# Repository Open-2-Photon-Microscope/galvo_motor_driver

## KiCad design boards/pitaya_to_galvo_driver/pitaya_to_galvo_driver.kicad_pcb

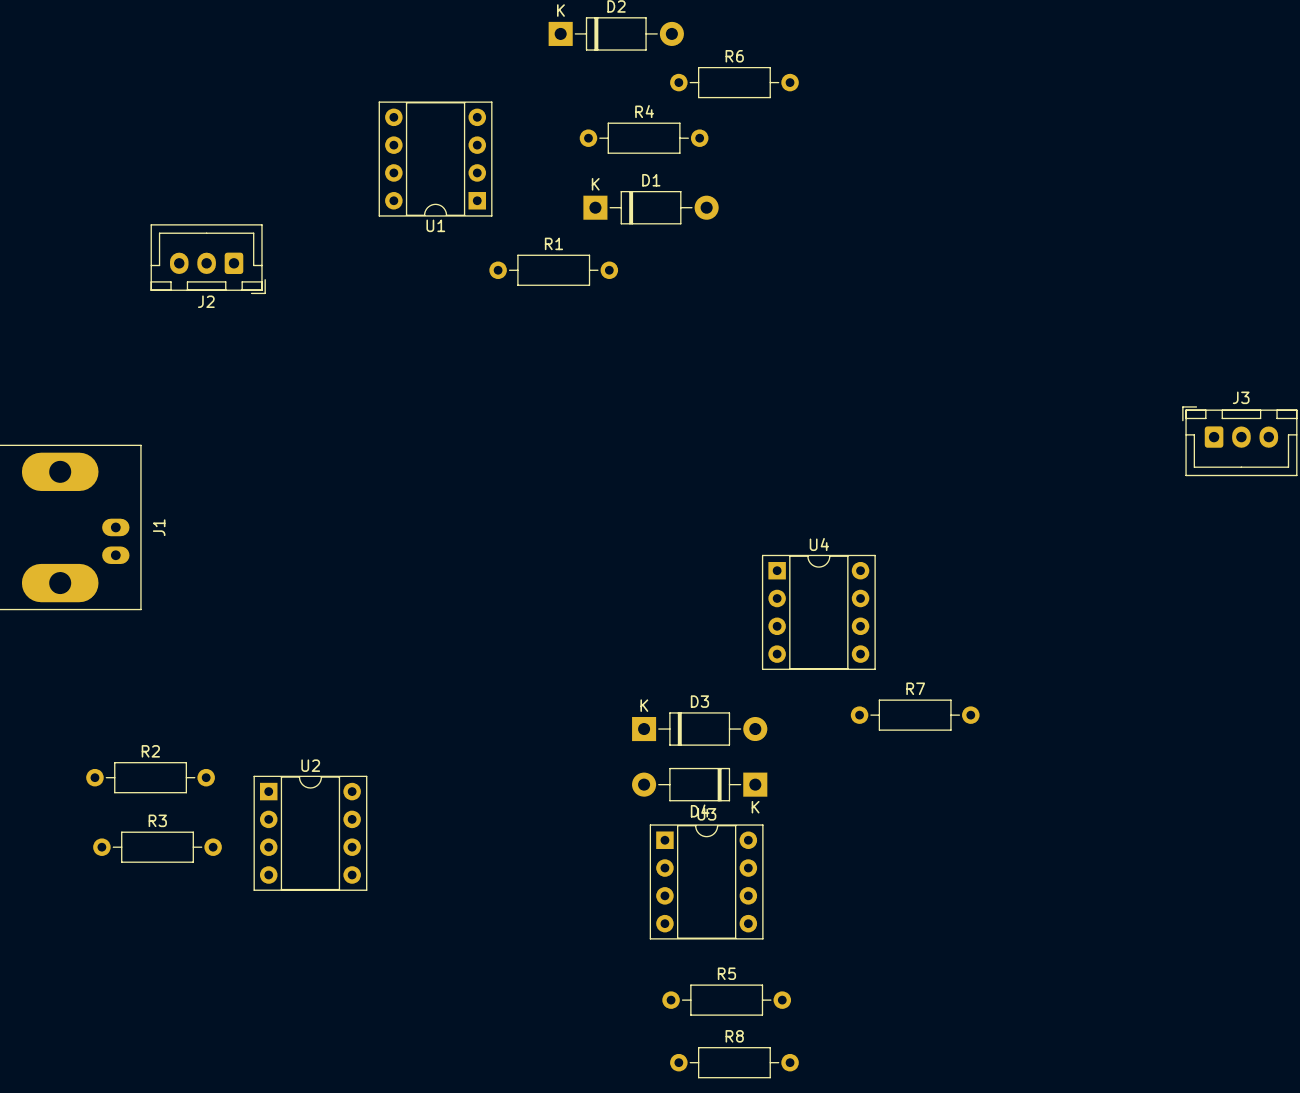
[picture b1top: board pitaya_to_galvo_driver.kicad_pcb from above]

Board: 2 copper layers, 19 parts (0 on the bottom side), 14 nets, no tracks yet.

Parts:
D1, D2, D3, D4: 1N5819; D_DO-41_SOD81_P10.16mm_Horizontal
J1: AI; BNC_Amphenol_B6252HB-NPP3G-50_Horizontal
J2: +15_gnd_-15v; JST_XH_B3B-XH-A_1x03_P2.50mm_Vertical
J3: to galvo; JST_XH_B3B-XH-A_1x03_P2.50mm_Vertical
R1, R2, R3, R5, R6, R7: 10k; R_Axial_DIN0207_L6.3mm_D2.5mm_P10.16mm_Horizontal
R4, R8: 56k; R_Axial_DIN0207_L6.3mm_D2.5mm_P10.16mm_Horizontal
U1, U2, U3, U4: LM741; DIP-8_W7.62mm_Socket

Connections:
+15V: J2.1, U1.7, U2.7, U3.7, U4.7
-15V: J2.3, U1.4, U2.4, U3.4, U4.4
GNDREF: J1.2, J2.2, J3.2, U1.3, U2.3, U3.3, U4.3
unnamed: D1.1, R1.2, R4.1, U1.2
unnamed: D1.2, D2.1, U1.6
unnamed: D2.2, R4.2, R6.1
unnamed: D3.1, R5.2, R8.1, U3.2
unnamed: D3.2, D4.1, U3.6
unnamed: D4.2, J3.3, R8.2
unnamed: J1.1, R1.1, R2.1
unnamed: J3.1, R7.2, U4.6
unnamed: R2.2, R3.1, U2.2
unnamed: R3.2, R5.1, U2.6
unnamed: R6.2, R7.1, U4.2

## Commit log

2020-02-21 initial doc
2020-02-25 made a small cover for the motor power supply
2020-02-26 board
2020-02-27 first stage of the board
2024-02-02 move things around and add data about new galvo
